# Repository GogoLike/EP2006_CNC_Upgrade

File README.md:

View this project on [CADLAB.io](https://cadlab.io/project/25653). 

## EP2006_CNC_Upgrade Project

# Описание проекта

Проект заключается в модернизации фрезерно-гравировально-сверлильного станка EP2006.
В качестве мождернизации подразумевается переход управления на стандарт G-Code с контроллером на открытой прошивке GRBL.
Контроллером в новой плате является STM32F103 в составе платы BluePill.

# Текущее состояние проекта

*Интерфейсы:*
- Известно управление исходным частотным преобразователем шпинделя
- Известно управление 5-ти фазными шаговыми двигателями через исходные драайвера шаговых двигателей осей X и Y
- Известно управление 2-х фазным шаговым двигателем через исходный драйвер шагового двигателя оси Z

*Датчики:*
- Известно подключение датчиков HOME
- Известно подключение датчика PROBE
- Выбрано подключение кнопки паузы на сигнал SAFETY_DOOR
- Выбрано подключение реле пылеососа на сигнал SPINDEL_ENABLE

*Схемотехника:*
- Коннектор для BluePill
- Датчики HOME заведены через оптопары и ферритовые кольца
- Управление X Y заведено через драйвер дифф. линий SN75ALS192N
- Управление Z заведено через инвертор SN7406N
- На Disable Steppers заведено только Enable Z

*PCB:*
- Реализовано на макетной плате

*Прошивка:*
- Удалось прошить контроллер
- В процессе настройки
- Проверена работоспособность движения по осям и перехода в HOME
- Проверен функционал щупа
- Проверено включение шпинделя
- Проверена резка плат

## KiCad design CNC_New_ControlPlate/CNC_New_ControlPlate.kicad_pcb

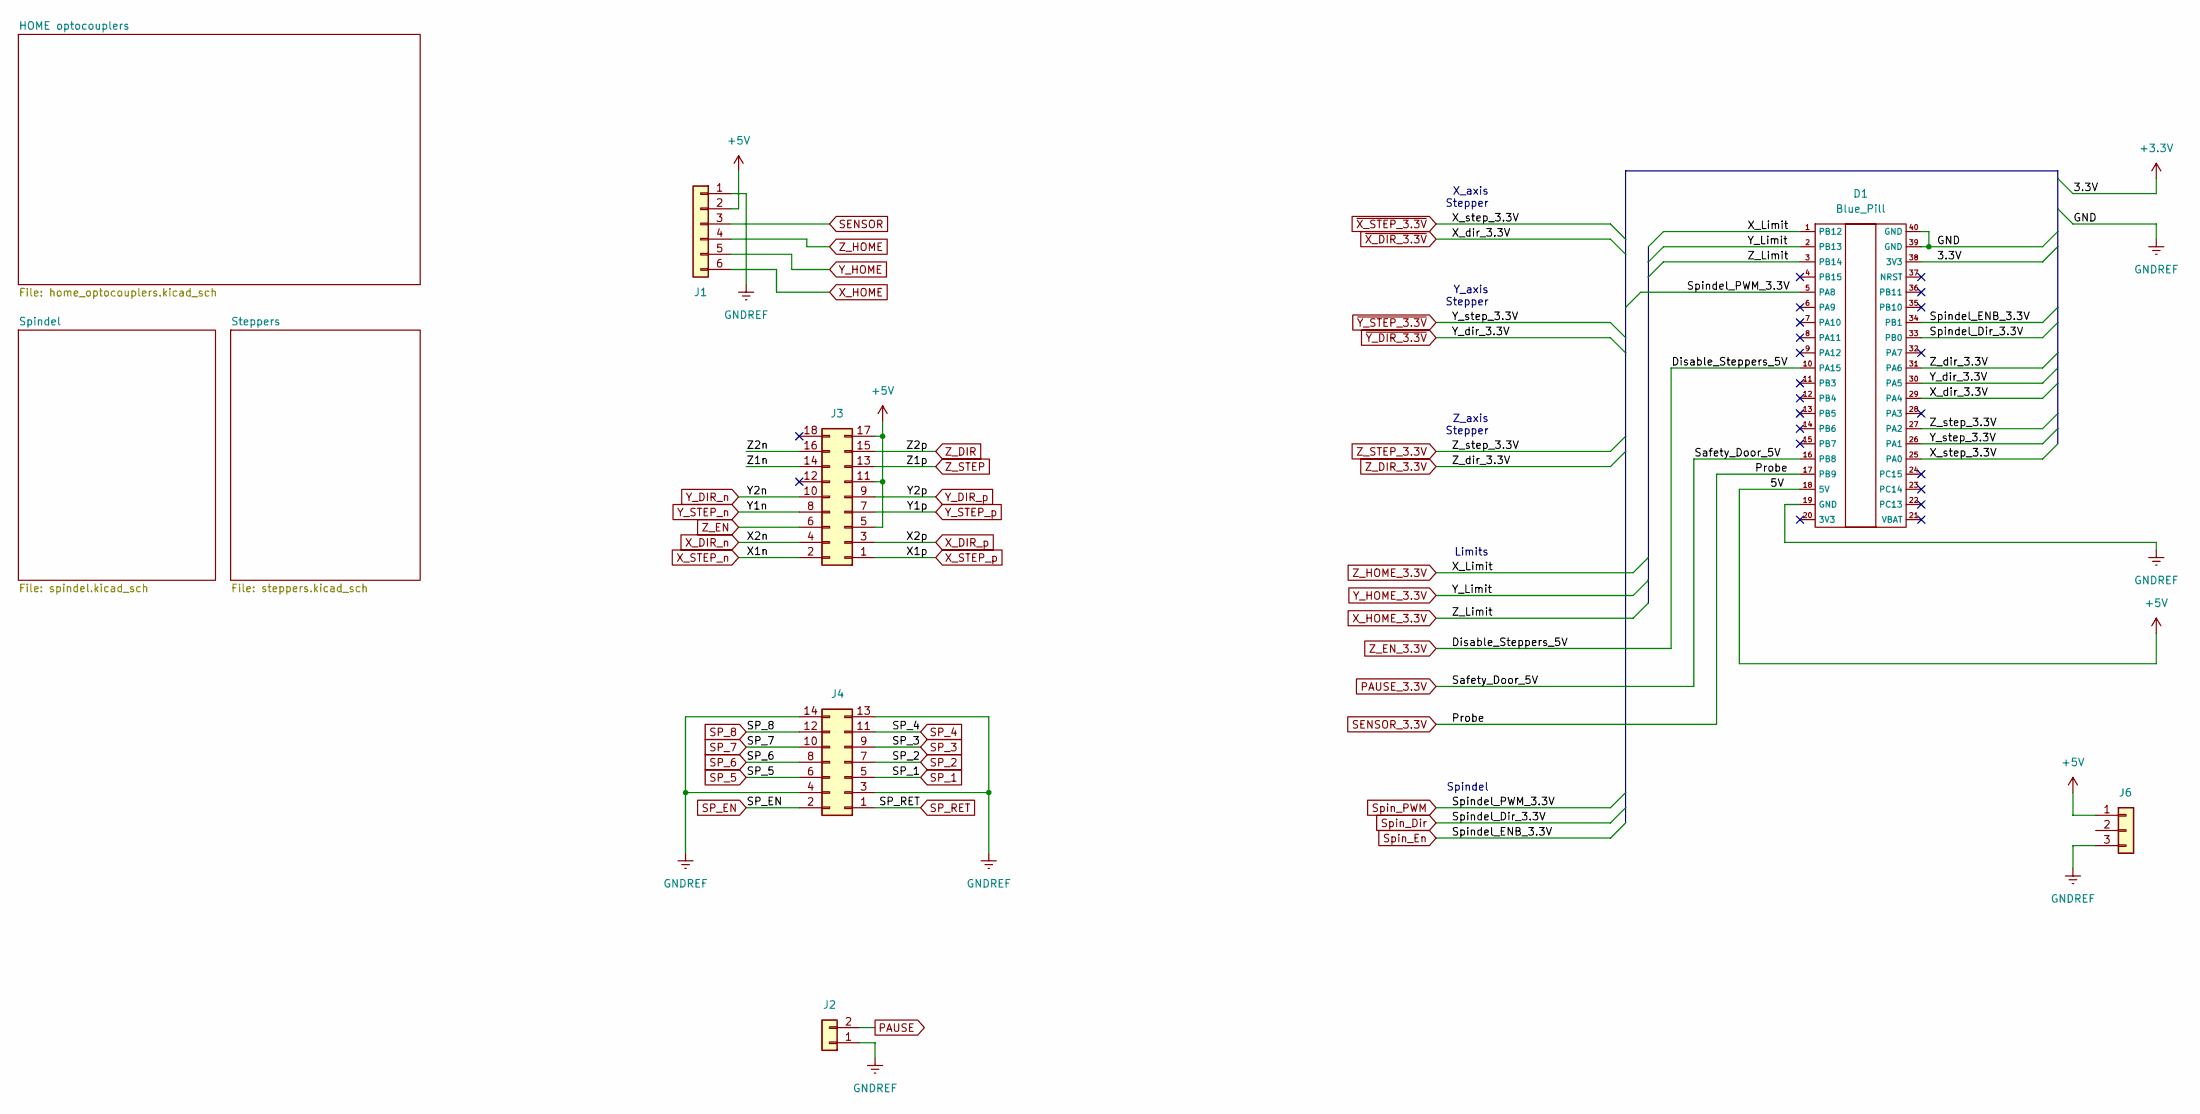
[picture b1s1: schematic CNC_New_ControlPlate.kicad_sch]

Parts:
D1: Blue_Pill; Maple_Mini
J1: OTHER; JST_XH_B6B-XH-A_1x06_P2.50mm_Vertical
J2: Conn_01x02; JST_XH_B2B-XH-A_1x02_P2.50mm_Vertical
J3: STEPPERS; PinHeader_2x09_P2.54mm_Vertical
J4: SPINDEL; PinHeader_2x07_P2.54mm_Vertical
J6: Conn_01x03; JST_VH_B3P-VH_1x03_P3.96mm_Vertical

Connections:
+3V3: D1.38 (3V3); also elsewhere on the board
+5V: D1.18 (5V), J1.2, J3.5, J3.11, J3.17, J6.1; also elsewhere on the board
/Z1n: J3.14
/Z2n: J3.16
GNDREF: D1.19 (GND), D1.39 (GND), D1.40 (GND), J1.1, J2.1, J4.3, J4.4, J4.13, J4.14, J6.3; also elsewhere on the board
PAUSE: J2.2; also elsewhere on the board
PAUSE_3.3V: D1.16 (PB8); also elsewhere on the board
SENSOR: J1.3; also elsewhere on the board
SENSOR_3.3V: D1.17 (PB9); also elsewhere on the board
SP_1: J4.5; also elsewhere on the board
SP_2: J4.7; also elsewhere on the board
SP_3: J4.9; also elsewhere on the board
SP_4: J4.11; also elsewhere on the board
SP_5: J4.6; also elsewhere on the board
SP_6: J4.8; also elsewhere on the board
SP_7: J4.10; also elsewhere on the board
SP_8: J4.12; also elsewhere on the board
SP_EN: J4.2; also elsewhere on the board
SP_RET: J4.1
Spin_Dir: D1.33 (PB0)
Spin_En: D1.34 (PB1); also elsewhere on the board
Spin_PWM: D1.5 (PA8); also elsewhere on the board
X_DIR_n: J3.4; also elsewhere on the board
X_DIR_p: J3.3; also elsewhere on the board
X_HOME: J1.6; also elsewhere on the board
X_HOME_3.3V: D1.3 (PB14); also elsewhere on the board
X_STEP_n: J3.2; also elsewhere on the board
X_STEP_p: J3.1; also elsewhere on the board
Y_DIR_n: J3.10; also elsewhere on the board
Y_DIR_p: J3.9; also elsewhere on the board
Y_HOME: J1.5; also elsewhere on the board
Y_HOME_3.3V: D1.2 (PB13); also elsewhere on the board
Y_STEP_n: J3.8; also elsewhere on the board
Y_STEP_p: J3.7; also elsewhere on the board
Z_DIR: J3.15; also elsewhere on the board
Z_DIR_3.3V: D1.31 (PA6); also elsewhere on the board
Z_EN: J3.6; also elsewhere on the board
Z_EN_3.3V: D1.10 (PA15); also elsewhere on the board
Z_HOME: J1.4; also elsewhere on the board
Z_HOME_3.3V: D1.1 (PB12); also elsewhere on the board
Z_STEP: J3.13; also elsewhere on the board
Z_STEP_3.3V: D1.27 (PA2); also elsewhere on the board
~X_DIR_3.3V: D1.29 (PA4); also elsewhere on the board
~X_STEP_3.3V: D1.25 (PA0); also elsewhere on the board
~Y_DIR_3.3V: D1.30 (PA5); also elsewhere on the board
~Y_STEP_3.3V: D1.26 (PA1); also elsewhere on the board

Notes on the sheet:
Spindel
Z_axis Stepper
Y_axis Stepper
X_axis Stepper
Limits

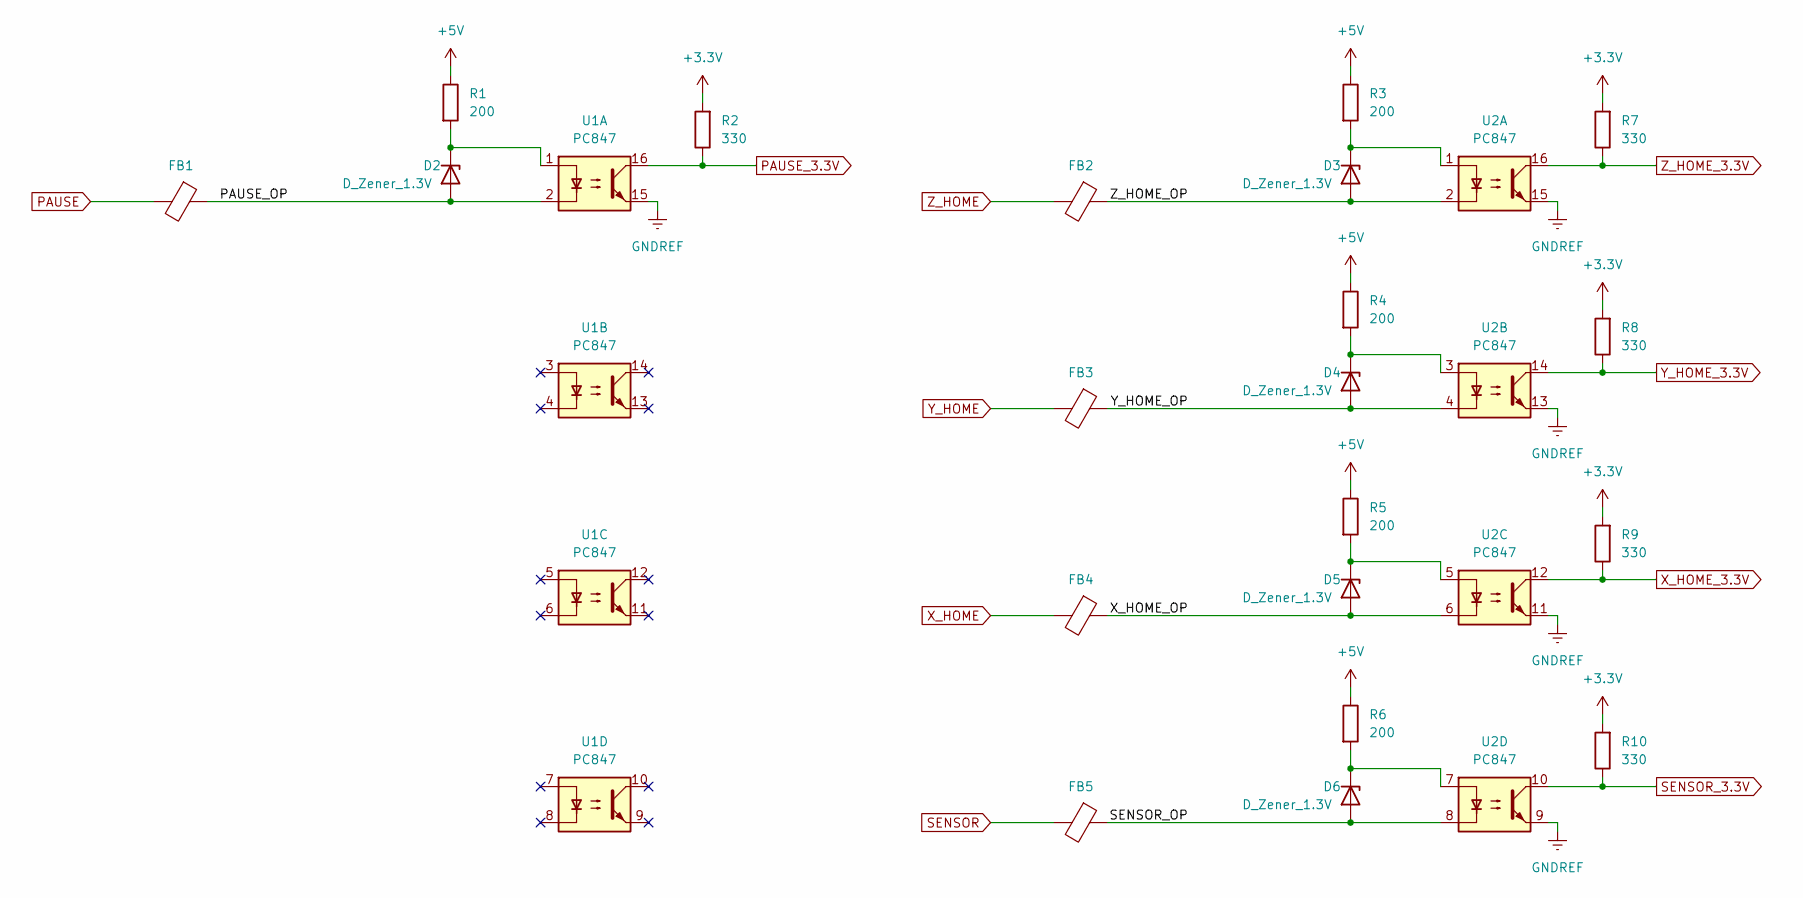
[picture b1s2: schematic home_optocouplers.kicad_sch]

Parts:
D2, D3, D4, D5, D6: D_Zener_1.3V; D_A-405_P7.62mm_Horizontal
FB1, FB2, FB3, FB4, FB5: FerriteBead; R_Axial_DIN0207_L6.3mm_D2.5mm_P7.62mm_Horizontal
R1, R3, R4, R5, R6: 200; R_0603_1608Metric
R2, R7, R8, R9, R10: 330; R_0603_1608Metric
U1, U2: PC847; DIP-16_W7.62mm_Socket_LongPads

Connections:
+3V3: R2.2, R7.2, R8.2, R9.2, R10.2; also elsewhere on the board
+5V: R1.1, R3.1, R4.1, R5.1, R6.1; also elsewhere on the board
/HOME optocouplers/PAUSE_OP: D2.2 (A), FB1.1, U1.2
/HOME optocouplers/SENSOR_OP: D6.2 (A), FB5.1, U2.8
/HOME optocouplers/X_HOME_OP: D5.2 (A), FB4.1, U2.6
/HOME optocouplers/Y_HOME_OP: D4.2 (A), FB3.1, U2.4
/HOME optocouplers/Z_HOME_OP: D3.2 (A), FB2.1, U2.2
GNDREF: U1.15, U2.9, U2.11, U2.13, U2.15; also elsewhere on the board
unnamed: D2.1 (K), R1.2, U1.1
unnamed: D3.1 (K), R3.2, U2.1
unnamed: D4.1 (K), R4.2, U2.3
unnamed: D5.1 (K), R5.2, U2.5
unnamed: D6.1 (K), R6.2, U2.7
PAUSE: FB1.2; also elsewhere on the board
PAUSE_3.3V: R2.1, U1.16; also elsewhere on the board
SENSOR: FB5.2; also elsewhere on the board
SENSOR_3.3V: R10.1, U2.10; also elsewhere on the board
X_HOME: FB4.2; also elsewhere on the board
X_HOME_3.3V: R9.1, U2.12; also elsewhere on the board
Y_HOME: FB3.2; also elsewhere on the board
Y_HOME_3.3V: R8.1, U2.14; also elsewhere on the board
Z_HOME: FB2.2; also elsewhere on the board
Z_HOME_3.3V: R7.1, U2.16; also elsewhere on the board

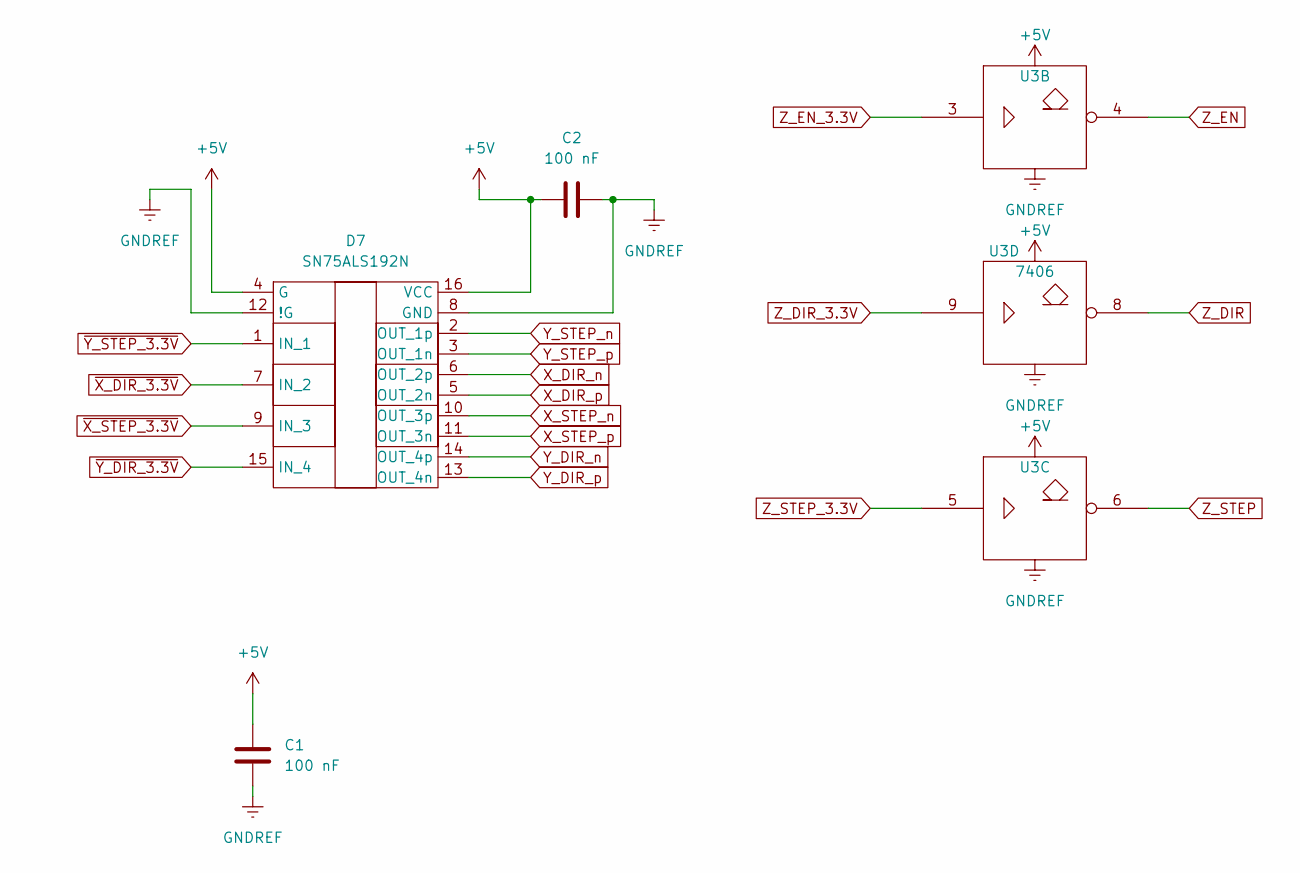
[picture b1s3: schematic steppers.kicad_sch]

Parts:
C1, C2: 100 nF; C_0603_1608Metric_Pad1.08x0.95mm_HandSolder
D7: SN75ALS192N; DIP-16_W7.62mm_Socket
U3: 7406; DIP-14_W7.62mm_Socket

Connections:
+5V: C1.2, C2.1, D7.4 (G), D7.16 (VCC), U3.14 (Vcc); also elsewhere on the board
GNDREF: C1.1, C2.2, D7.8 (GND), D7.12 (!G), U3.7 (Gnd); also elsewhere on the board
X_DIR_n: D7.6 (OUT_2p); also elsewhere on the board
X_DIR_p: D7.5 (OUT_2n); also elsewhere on the board
X_STEP_n: D7.10 (OUT_3p); also elsewhere on the board
X_STEP_p: D7.11 (OUT_3n); also elsewhere on the board
Y_DIR_n: D7.14 (OUT_4p); also elsewhere on the board
Y_DIR_p: D7.13 (OUT_4n); also elsewhere on the board
Y_STEP_n: D7.2 (OUT_1p); also elsewhere on the board
Y_STEP_p: D7.3 (OUT_1n); also elsewhere on the board
Z_DIR: U3.8; also elsewhere on the board
Z_DIR_3.3V: U3.9; also elsewhere on the board
Z_EN: U3.4; also elsewhere on the board
Z_EN_3.3V: U3.3; also elsewhere on the board
Z_STEP: U3.6; also elsewhere on the board
Z_STEP_3.3V: U3.5; also elsewhere on the board
~X_DIR_3.3V: D7.7 (IN_2); also elsewhere on the board
~X_STEP_3.3V: D7.9 (IN_3); also elsewhere on the board
~Y_DIR_3.3V: D7.15 (IN_4); also elsewhere on the board
~Y_STEP_3.3V: D7.1 (IN_1); also elsewhere on the board

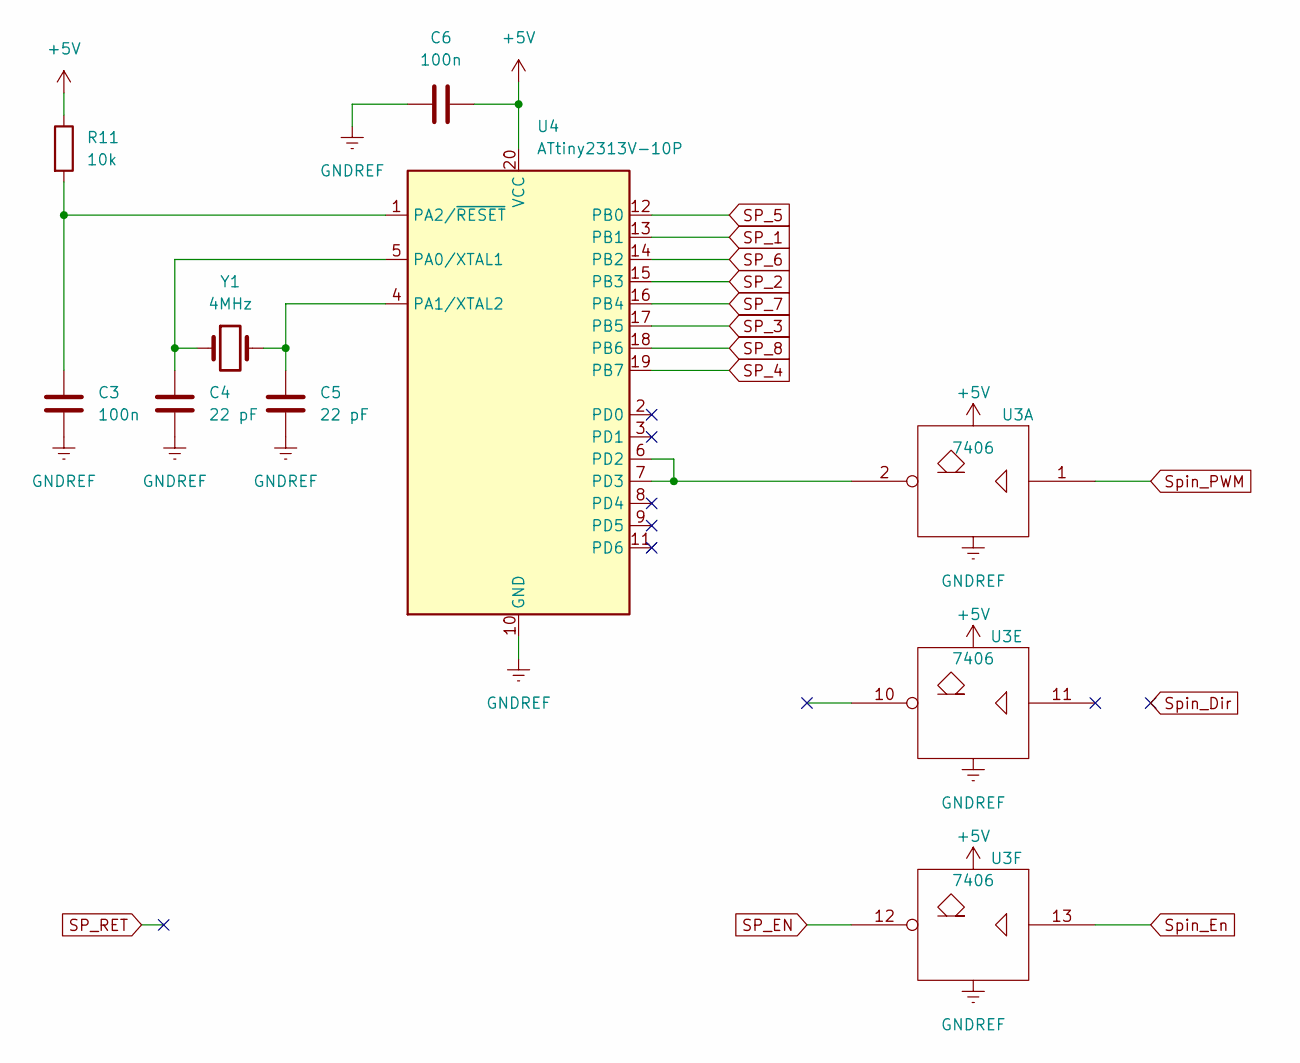
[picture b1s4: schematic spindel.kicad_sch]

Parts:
C3, C6: 100n; C_0603_1608Metric_Pad1.08x0.95mm_HandSolder
C4, C5: 22 pF; C_0603_1608Metric_Pad1.08x0.95mm_HandSolder
R11: 10k; R_0603_1608Metric
U3: 7406; DIP-14_W7.62mm_Socket
U4: ATtiny2313V-10P; DIP-20_W7.62mm
Y1: 4MHz; Crystal_HC49-4H_Vertical

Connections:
+5V: C6.2, R11.1, U3.14 (Vcc), U4.20 (VCC); also elsewhere on the board
GNDREF: C3.1, C4.1, C5.1, C6.1, U3.7 (Gnd), U4.10 (GND); also elsewhere on the board
unnamed: C3.2, R11.2, U4.1 (PA2/~RESET)
unnamed: C4.2, U4.5 (PA0/XTAL1), Y1.1
unnamed: C5.2, U4.4 (PA1/XTAL2), Y1.2
unnamed: U3.2, U4.6 (PD2), U4.7 (PD3)
SP_1: U4.13 (PB1); also elsewhere on the board
SP_2: U4.15 (PB3); also elsewhere on the board
SP_3: U4.17 (PB5); also elsewhere on the board
SP_4: U4.19 (PB7); also elsewhere on the board
SP_5: U4.12 (PB0); also elsewhere on the board
SP_6: U4.14 (PB2); also elsewhere on the board
SP_7: U4.16 (PB4); also elsewhere on the board
SP_8: U4.18 (PB6); also elsewhere on the board
SP_EN: U3.12; also elsewhere on the board
Spin_En: U3.13; also elsewhere on the board
Spin_PWM: U3.1; also elsewhere on the board

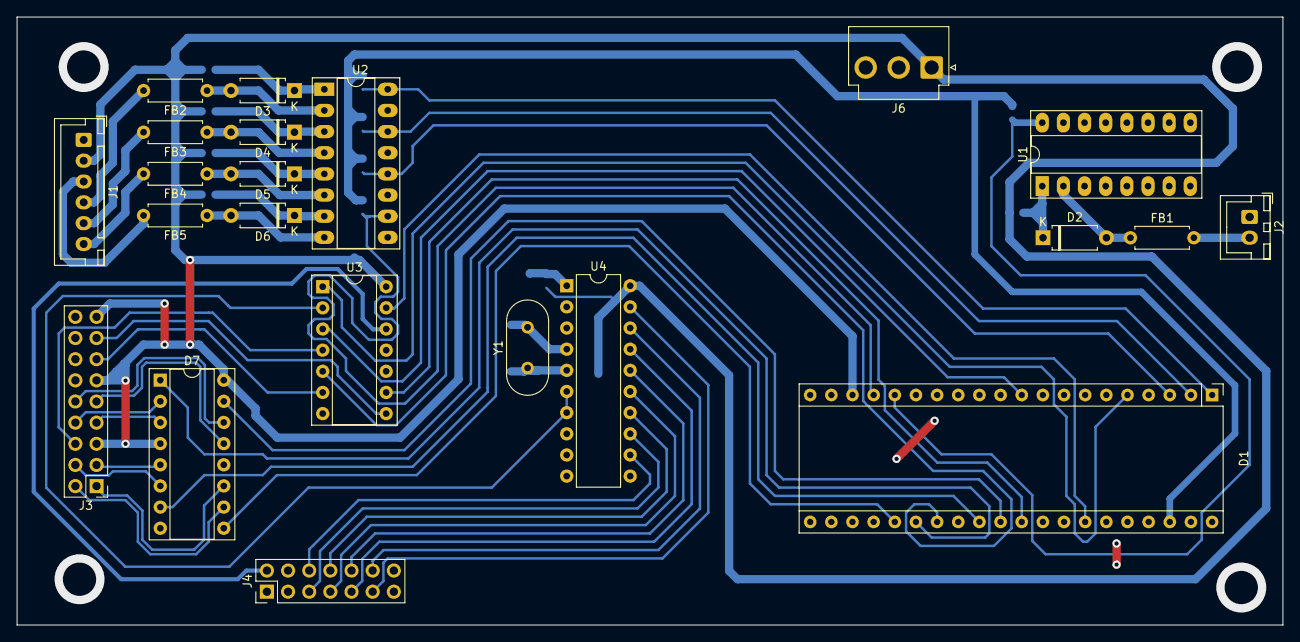
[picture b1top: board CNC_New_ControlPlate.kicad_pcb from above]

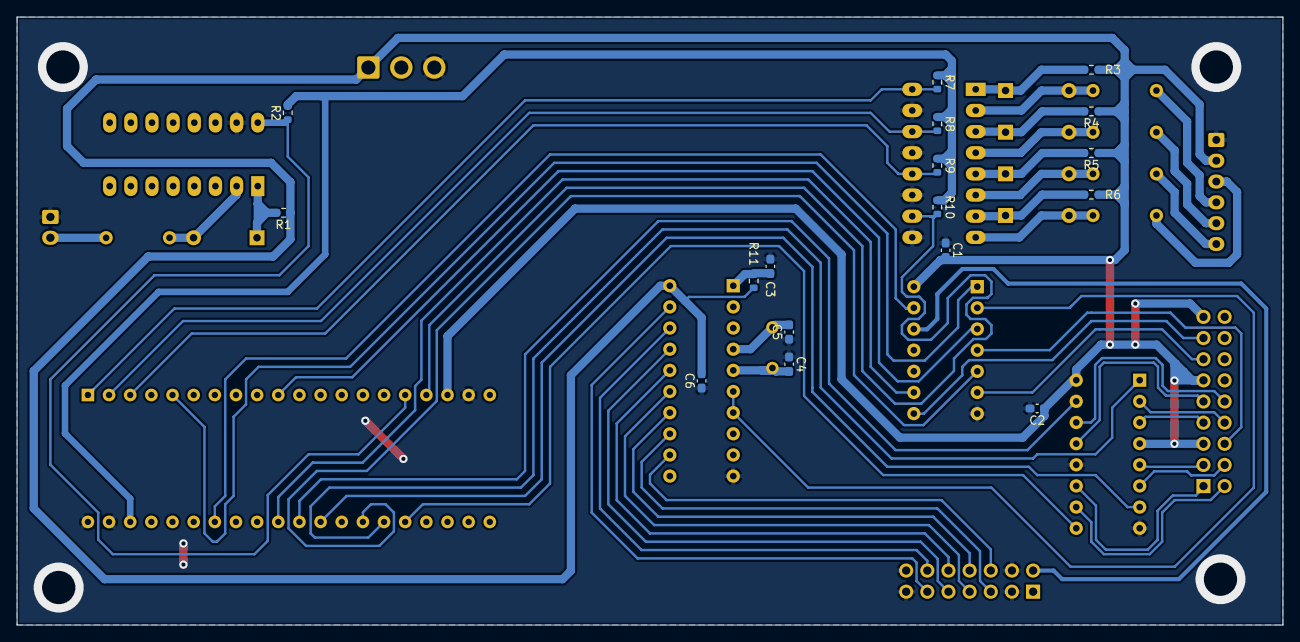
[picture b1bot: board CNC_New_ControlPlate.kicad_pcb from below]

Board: 2 copper layers, 152.0 x 73.0 mm, 39 parts (17 on the bottom side), 56 nets.

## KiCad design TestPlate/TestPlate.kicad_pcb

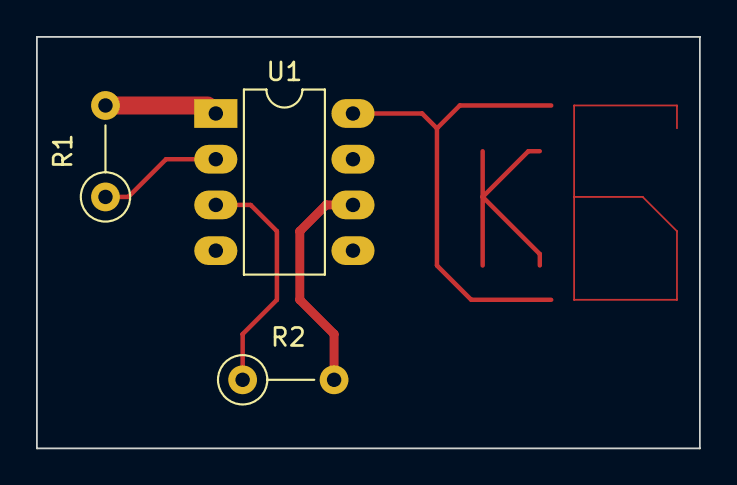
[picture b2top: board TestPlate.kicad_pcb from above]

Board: 2 copper layers, 36.8 x 22.9 mm, 3 parts (0 on the bottom side), 4 nets.

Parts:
R1, R2: R; R_Axial_DIN0207_L6.3mm_D2.5mm_P5.08mm_Vertical
U1: 4555; DIP-8_W7.62mm_LongPads

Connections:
unnamed: R1.1, U1.2 (A0)
unnamed: R1.2, U1.1 (~EN)
unnamed: R2.1, U1.3 (A1)
unnamed: R2.2, U1.6 (Q2)

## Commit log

2022-05-23 Create Repo
2022-05-23 Backlink to CADLAB.io has been added.
2022-05-23 Test
2022-05-23 Cancel Test
2022-05-23 Add .gitignore
2022-05-23 Add photoes
2022-05-24 + Интерфейс STM32F103
    Доделал выводы на глобальные метки всех необходимых GRBL контактов
2022-05-24 Взял в работу заведение датчиков HOME через оптопары
2022-05-24 +Файл линий HOME и SENSOR
    + Завел датчики через оптопары
    + Посчитал токоограничивающие резисторы на вход и выход оптопары
    + Поставил стабилитроны, возможно не понадобятся
2022-05-28 Датчики и щуп через оптопары
2022-09-08 [*] ReadME [+] Даташиты на драйверы шаговых двигателей
2022-09-17 Обновил датчики HOME
2022-09-17 [+] Лист STEPPERS [+] Разъем подключения шаговиков [+] Моделька драйвера дифф линий [+] Управление X Y заведено через драйверы дифф линий [+] Управление Z заведено через инвертор [+] Enable Z заведен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
2022-09-17 Edit ReadMe
2022-09-20 Add GRBL submodule
2022-10-04 Add test plate
2022-10-09 Add spindel sch
2022-10-11 Add attiny2313
2022-10-11 Add attiny2313 2
2022-10-11 Add spindel
2022-10-11 [*] номиналы блокировочных конденсаторов [+] мкроконтроллер управления оборотами шпинделя [+] кнопка паузы
2022-10-12 Cosmetic edit
2022-10-12 [*] Исправлены ошибки с выходами питания. [+] Добавлены обозначения элементов
2022-10-12 [*] Порядок выводов на разъёме Others [*] Порядок выводов на разъёме Pause [*] Порядок подключения каналов на драйвере диф. линий [+] Начата расстановка pcb схемы
2022-10-13 Edit footprints
2022-10-15 [*] Разводка платы в один слой (осталось 7 перемычек)
2022-10-15 Edit PCB, add jumpers
2022-10-15 [*] Разведена плата в один слой (3 перемычки на шине 5В; 2 соединения земли через плату STM
2022-10-18 [+] Добавлен разъем питания
